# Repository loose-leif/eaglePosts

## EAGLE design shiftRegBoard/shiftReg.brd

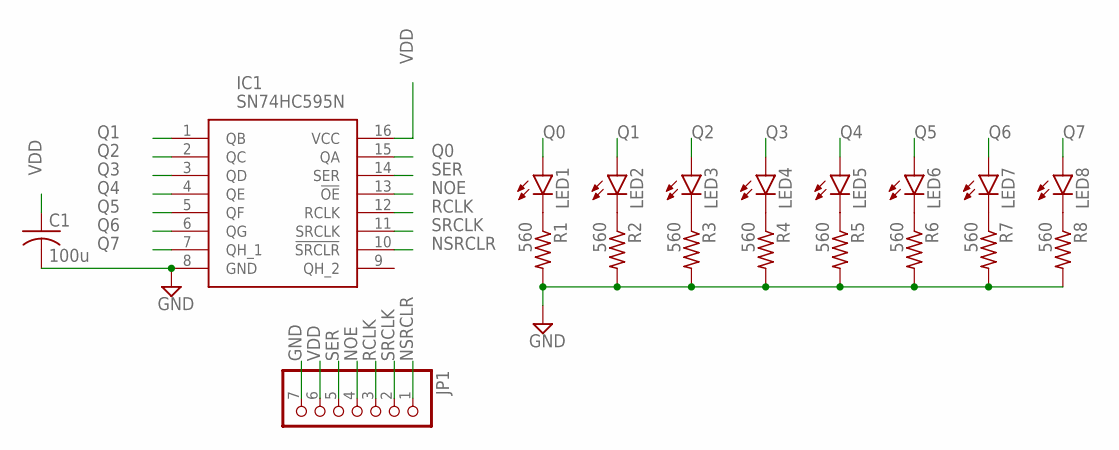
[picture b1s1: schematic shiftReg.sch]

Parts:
C1: 100u; C0805
IC1: SN74HC595N; DIP794W53P254L1930H508Q16N
JP1: PINHD-1X7; 1X07
LED1, LED2, LED3, LED4, LED5, LED6, LED7, LED8: LEDCHIP-LED0805; CHIP-LED0805
R1, R2, R3, R4, R5, R6, R7, R8: 560; R0805

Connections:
GND: C1.2, IC1.8 (GND), JP1.7, R1.2, R2.2, R3.2, R4.2, R5.2, R6.2, R7.2, R8.2
unnamed: LED1.C, R1.1
unnamed: LED2.C, R2.1
unnamed: LED3.C, R3.1
unnamed: LED4.C, R4.1
unnamed: LED5.C, R5.1
unnamed: LED6.C, R6.1
unnamed: LED7.C, R7.1
unnamed: LED8.C, R8.1
NOE: IC1.13 (!OE), JP1.4
NSRCLR: IC1.10 (!SRCLR), JP1.1
Q0: IC1.15 (QA), LED1.A
Q1: IC1.1 (QB), LED2.A
Q2: IC1.2 (QC), LED3.A
Q3: IC1.3 (QD), LED4.A
Q4: IC1.4 (QE), LED5.A
Q5: IC1.5 (QF), LED6.A
Q6: IC1.6 (QG), LED7.A
Q7: IC1.7 (QH_1), LED8.A
RCLK: IC1.12 (RCLK), JP1.3
SER: IC1.14 (SER), JP1.5
SRCLK: IC1.11 (SRCLK), JP1.2
VDD: C1.1, IC1.16 (VCC), JP1.6

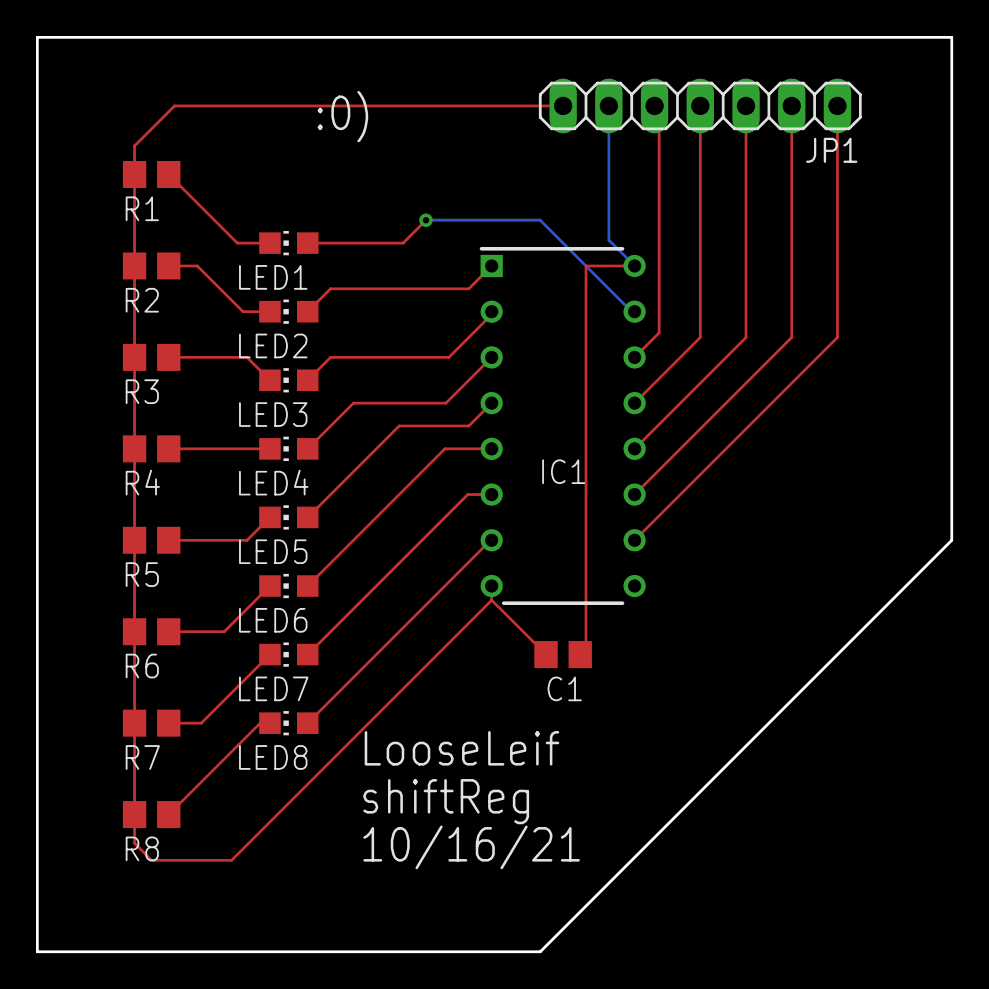
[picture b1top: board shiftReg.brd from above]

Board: 2 copper layers, 50.8 x 50.8 mm, 19 parts (0 on the bottom side), 23 nets.

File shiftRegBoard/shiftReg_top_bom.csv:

Comment,Designator,Footprint,LCSC Part #
560,C1 LED1 LED2 LED3 LED4 LED5 LED6 LED7 LED8 R1 R2 R3 R4 R5 R6 R7 R8,R0805,

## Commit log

2021-09-19 TC IA ADC
    start of thermocouple hardware
2021-09-26 Create improvedThermoCoupleADC.sch
    Working with LT1025/LTK001/ADS1115
2021-10-03 added controls via MCU
2021-10-04 simpleUpdate
2021-10-16 made SR pcb
    need to generate gerber
2021-10-22 running LTSPICE cloud
2021-11-01 done with
2022-02-25 forgot to update
    updates of multiple homeworks and sketches
